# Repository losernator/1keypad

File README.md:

# 1keypad
Keypad for one key

## Install
```

```

` `

##  
 
```
 
```
**NOTE :**  

**  ** 

  *  
  * 
    **NOTE :**

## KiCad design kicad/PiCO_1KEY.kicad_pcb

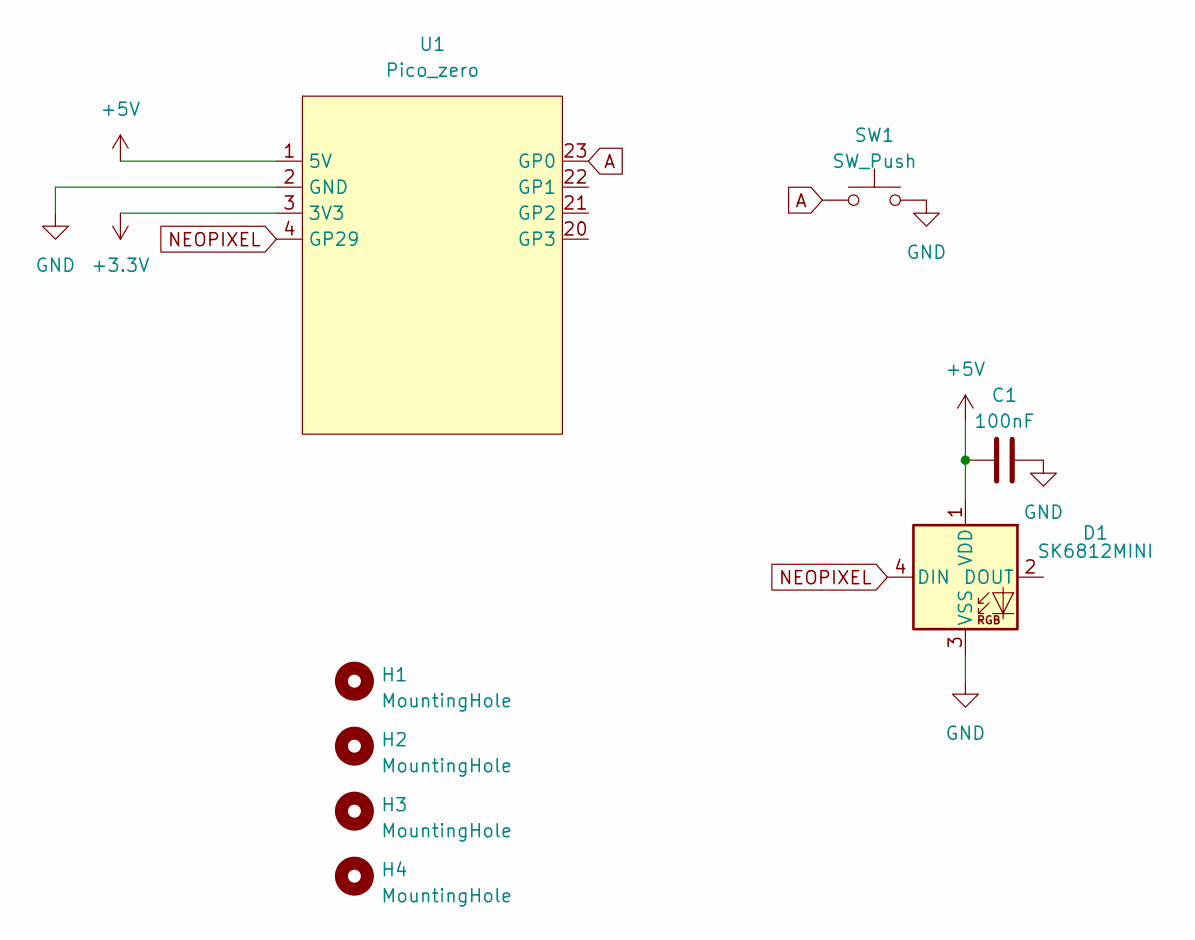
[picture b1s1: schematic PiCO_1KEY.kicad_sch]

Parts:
C1: 100nF; C_0805_2012Metric_Pad1.18x1.45mm_HandSolder; LCSC Part C38141
D1: SK6812MINI; SK6812-MINI-E; LCSC Part C5149201
H1, H2, H3, H4: MountingHole; MountingHole_3.2mm_M3_DIN965_Pad_TopBottom
SW1: SW_Push; SW_Hotswap_Kailh_MX_1.25u
U1: Pico_zero; Pico_Zero_TH_lite; LCSC Part C5350143

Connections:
+3V3: U1.3 (3V3)
+5V: C1.2, D1.1 (VDD), U1.1 (5V)
A: SW1.1, U1.23 (GP0)
GND: C1.1, D1.3 (VSS), SW1.2, U1.2 (GND)
NEOPIXEL: D1.4 (DIN), U1.4 (GP29)

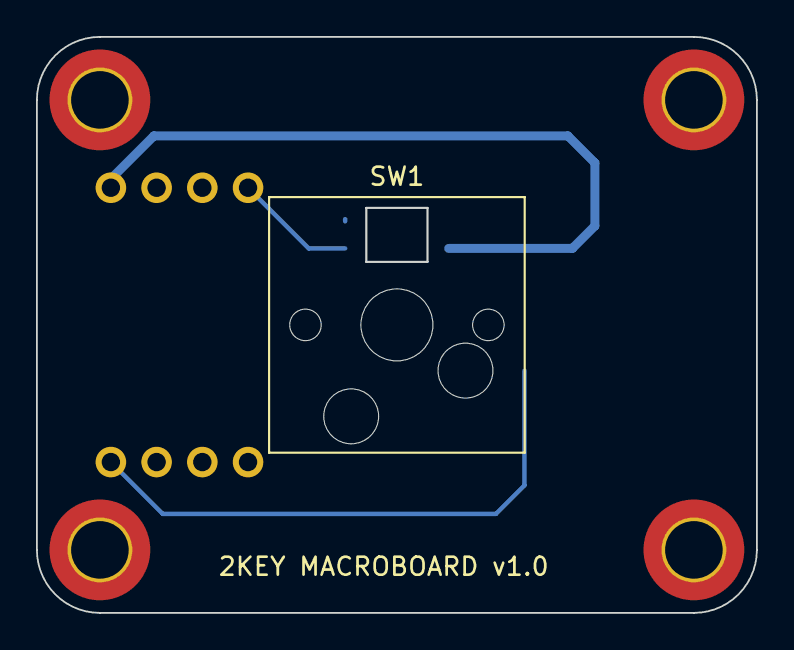
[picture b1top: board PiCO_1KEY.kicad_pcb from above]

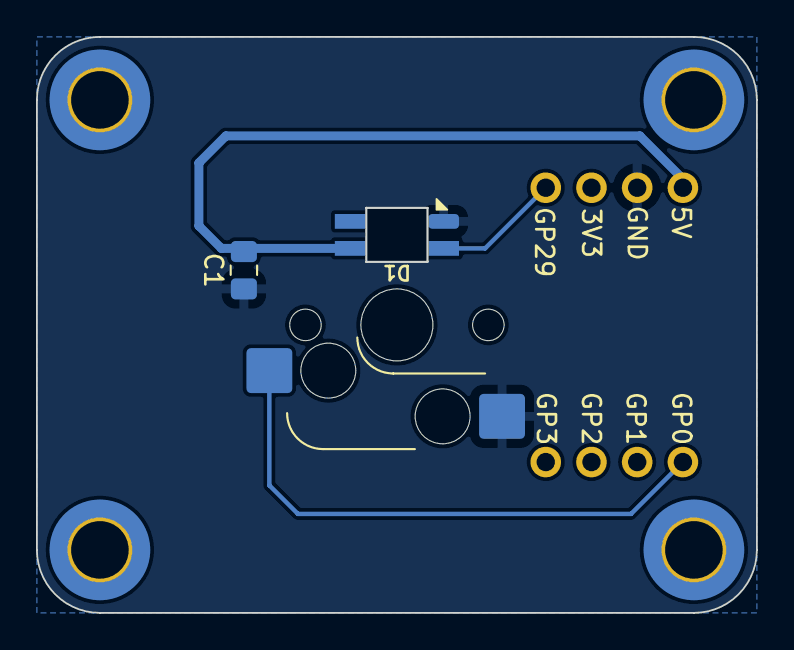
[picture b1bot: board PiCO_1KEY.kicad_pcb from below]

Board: 2 copper layers, 40.0 x 32.0 mm, 8 parts (3 on the bottom side), 4 nets.

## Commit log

2023-07-11 Update
    Update kicad files
